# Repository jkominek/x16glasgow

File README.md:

# Commander X16 to Glasgow adapter

This is an expansion card for the [Commander
X16](https://x16community.github.io/faq/faq.html) retro PC, which
exposes one memory mapped IO region (at a time) to a [Glasgow
Interface Explorer](https://glasgow-embedded.org/latest/intro.html).

With it, the Glasgow can emulate nearly any IO card you might plug
into the X16, so long as that card only wants to talk to a modern
USB-capable PC 🤓. So far I've [got an
applet](https://github.com/jkominek/glasgow) which half-assedly
emulates a 16550, and hooks it up to a pseudoterminal on a Linux
system. With David Murray's ROMTERM, you can then use the X16 as
a "serial" terminal to log into the Linux system.

(To be super clear, that's all done without the [Commander X16 Serial
& ESP32 Network
card](https://texelec.com/product/commander-x16-serial-network-card/).)

And here's a quick little video of it in operation: https://www.youtube.com/watch?v=3OkkUSMPfc0

# how it works

The Glasgow has 16 IO pins. To act as an IO device, you need to handle:
- 8 data lines
- RWB
- PHI2
- At least one of the IO selection lines
- An IRQ
- Five address lines (for the full 32 byte space)

That's 17 lines. You could drop the IRQ line, but that'd be boring.
Instead, we decode RWB, PHI2 and a jumper-chosen IO selection line
using some 74-series logic, and condense the three of them into
/RD and /WR lines. That fits everything into 16 pins.

# how do i get a getty on a pseudoterminal

```
mgetty -r -b -m '""' /dev/pts/X
```

not actually sure if the `-b` is necessary. The `-m` bit was the secret
sauce.

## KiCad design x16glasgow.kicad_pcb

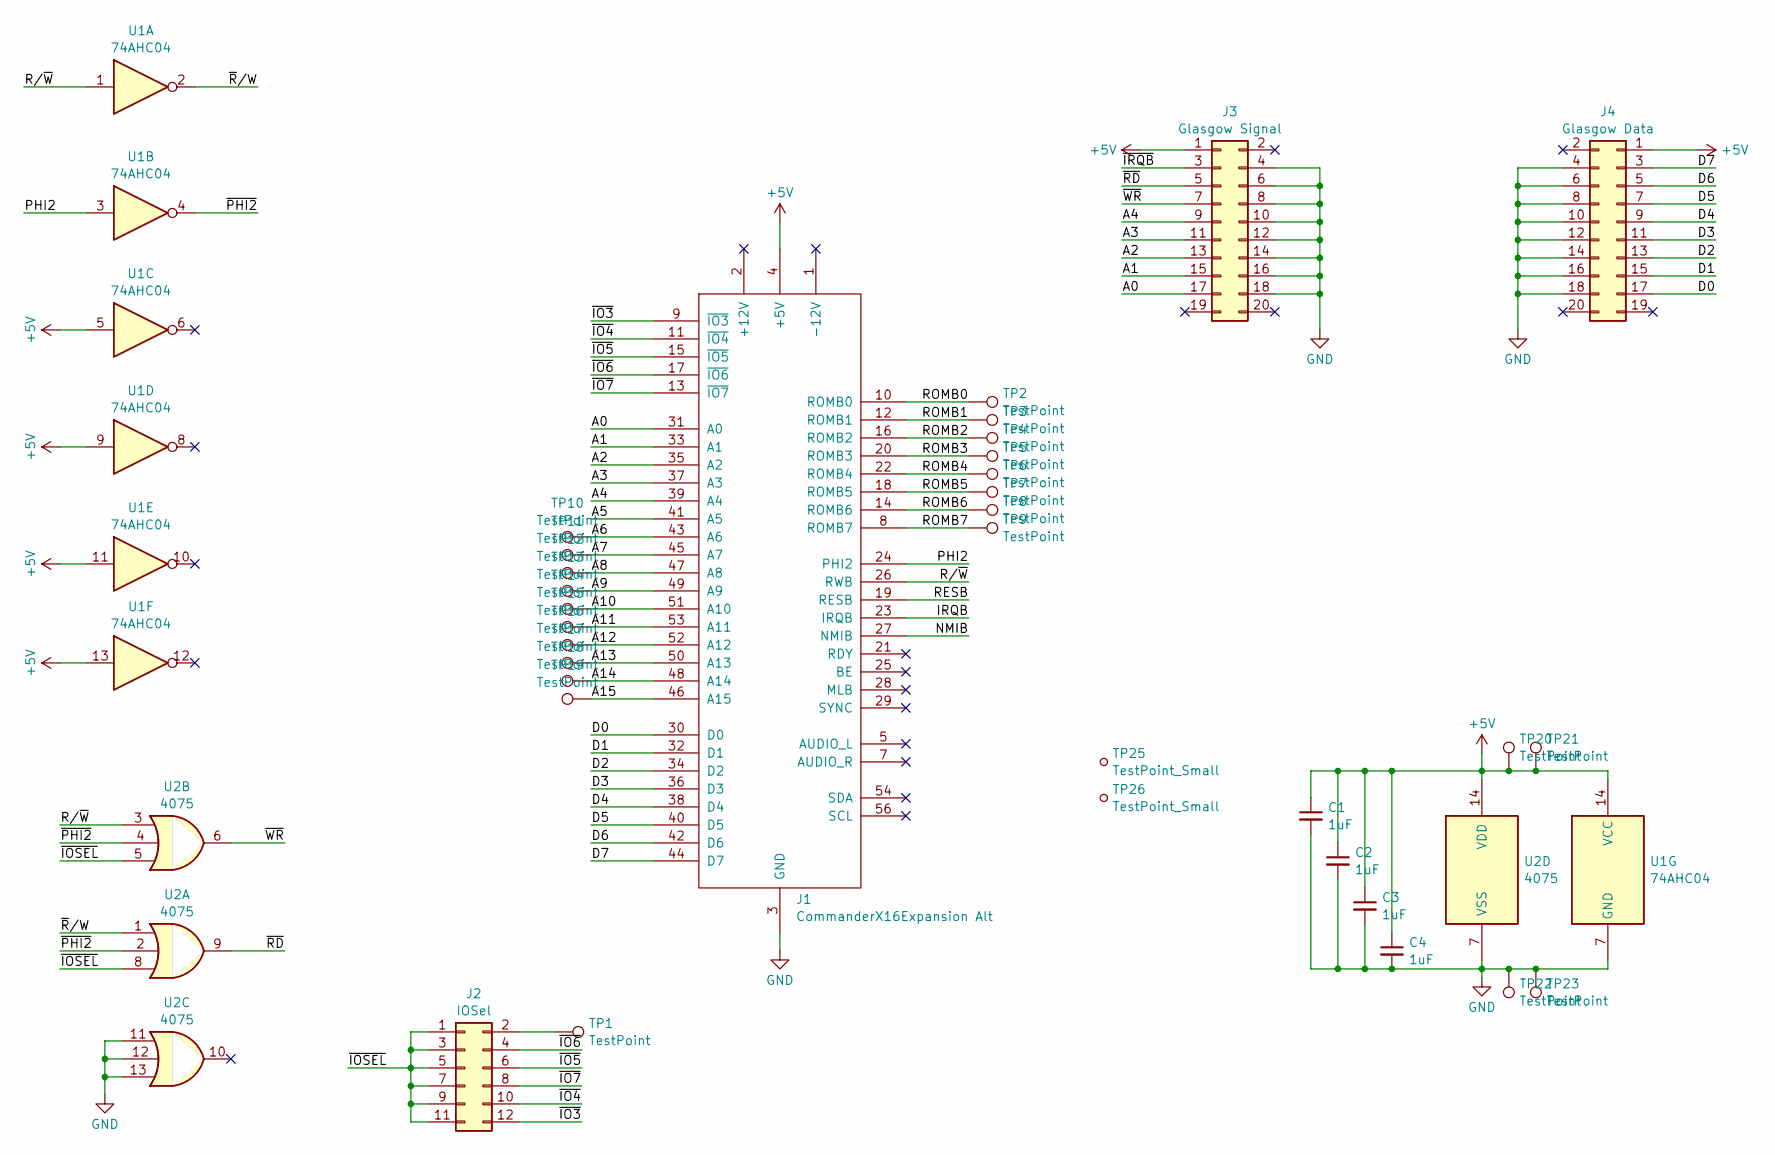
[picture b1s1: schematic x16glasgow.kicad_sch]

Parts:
C1, C2, C3, C4: 1uF; C_0805_2012Metric
J1: CommanderX16Expansion Alt; CommanderX16Expansion
J2: IOSel; PinHeader_2x06_P2.54mm_Vertical
J3: Glasgow Signal; PinSocket_2x10_P2.54mm_Vertical
J4: Glasgow Data; PinSocket_2x10_P2.54mm_Vertical
TP1, TP2, TP3, TP4, TP5, TP6, TP7, TP8, TP9, TP10, TP11, TP12, TP13, TP14, TP15, TP16, TP17, TP18, TP19, TP20, TP21, TP22, TP23: TestPoint; TestPoint_Pad_D2.0mm
TP25, TP26: TestPoint_Small; TSSOP-14_4.4x5mm_P0.65mm
U1: 74AHC04; TSSOP-14_4.4x5mm_P0.65mm
U2: 4075; TSSOP-14_4.4x5mm_P0.65mm

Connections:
+5V: C1.1, C2.1, C3.1, C4.1, J1.4 (+5V), J1.57 (+5V), J3.1, J4.1, TP20.1, TP21.1, U1.5, U1.9, U1.11, U1.13, U1.14 (VCC), U2.14 (VDD)
/A0: J1.31 (A0), J3.17
/A1: J1.33 (A1), J3.15
/A2: J1.35 (A2), J3.13
/A3: J1.37 (A3), J3.11
/A4: J1.39 (A4), J3.9
/A5: J1.41 (A5)
/A6: J1.43 (A6), TP10.1
/A7: J1.45 (A7), TP11.1
/A8: J1.47 (A8), TP12.1
/A9: J1.49 (A9), TP13.1
/A10: J1.51 (A10), TP14.1
/A11: J1.53 (A11), TP15.1
/A12: J1.52 (A12), TP16.1
/A13: J1.50 (A13), TP17.1
/A14: J1.48 (A14), TP18.1
/A15: J1.46 (A15), TP19.1
/D0: J1.30 (D0), J4.17
/D1: J1.32 (D1), J4.15
/D2: J1.34 (D2), J4.13
/D3: J1.36 (D3), J4.11
/D4: J1.38 (D4), J4.9
/D5: J1.40 (D5), J4.7
/D6: J1.42 (D6), J4.5
/D7: J1.44 (D7), J4.3
/IRQB: J1.23 (IRQB)
/NMIB: J1.27 (NMIB)
/PHI2: J1.24 (PHI2), U1.3
/RESB: J1.19 (RESB)
/ROMB0: J1.10 (ROMB0), TP2.1
/ROMB1: J1.12 (ROMB1), TP3.1
/ROMB2: J1.16 (ROMB2), TP4.1
/ROMB3: J1.20 (ROMB3), TP5.1
/ROMB4: J1.22 (ROMB4), TP6.1
/ROMB5: J1.18 (ROMB5), TP7.1
/ROMB6: J1.14 (ROMB6), TP8.1
/ROMB7: J1.8 (ROMB7), TP9.1
/R/~W: J1.26 (RWB), U1.1, U2.3
/~IO3: J1.9 (~IO3), J2.12
/~IO4: J1.11 (~IO4), J2.10
/~IO5: J1.15 (~IO5), J2.6
/~IO6: J1.17 (~IO6), J2.4
/~IO7: J1.13 (~IO7), J2.8
/~IOSEL: J2.1, J2.3, J2.5, J2.7, J2.9, J2.11, U2.5, U2.8
/~IRQB: J3.3
/~PHI2: U1.4, U2.2, U2.4
/~RD: J3.5, U2.9
/~R/W: U1.2, U2.1
/~WR: J3.7, U2.6
GND: C1.2, C2.2, C3.2, C4.2, J1.3 (GND), J1.6 (GND), J1.55 (GND), J1.58 (GND), J3.4, J3.6, J3.8, J3.10, J3.12, J3.14, J3.16, J3.18, J4.4, J4.6, J4.8, J4.10, J4.12, J4.14, J4.16, J4.18, TP22.1, TP23.1, U1.7 (GND), U2.7 (VSS), U2.11, U2.12, U2.13
unnamed: J2.2, TP1.1

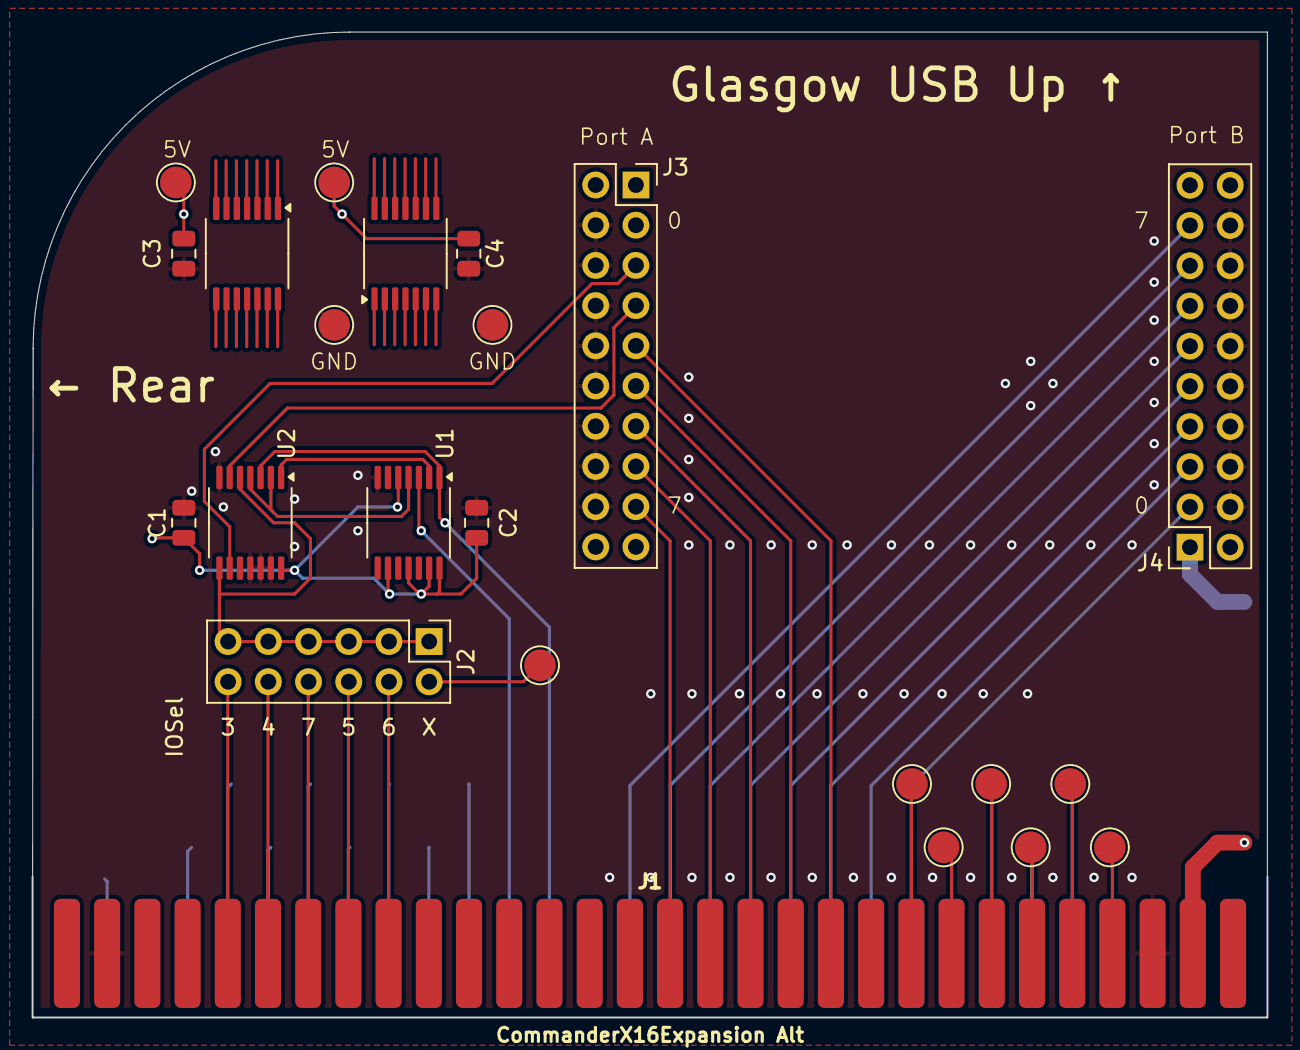
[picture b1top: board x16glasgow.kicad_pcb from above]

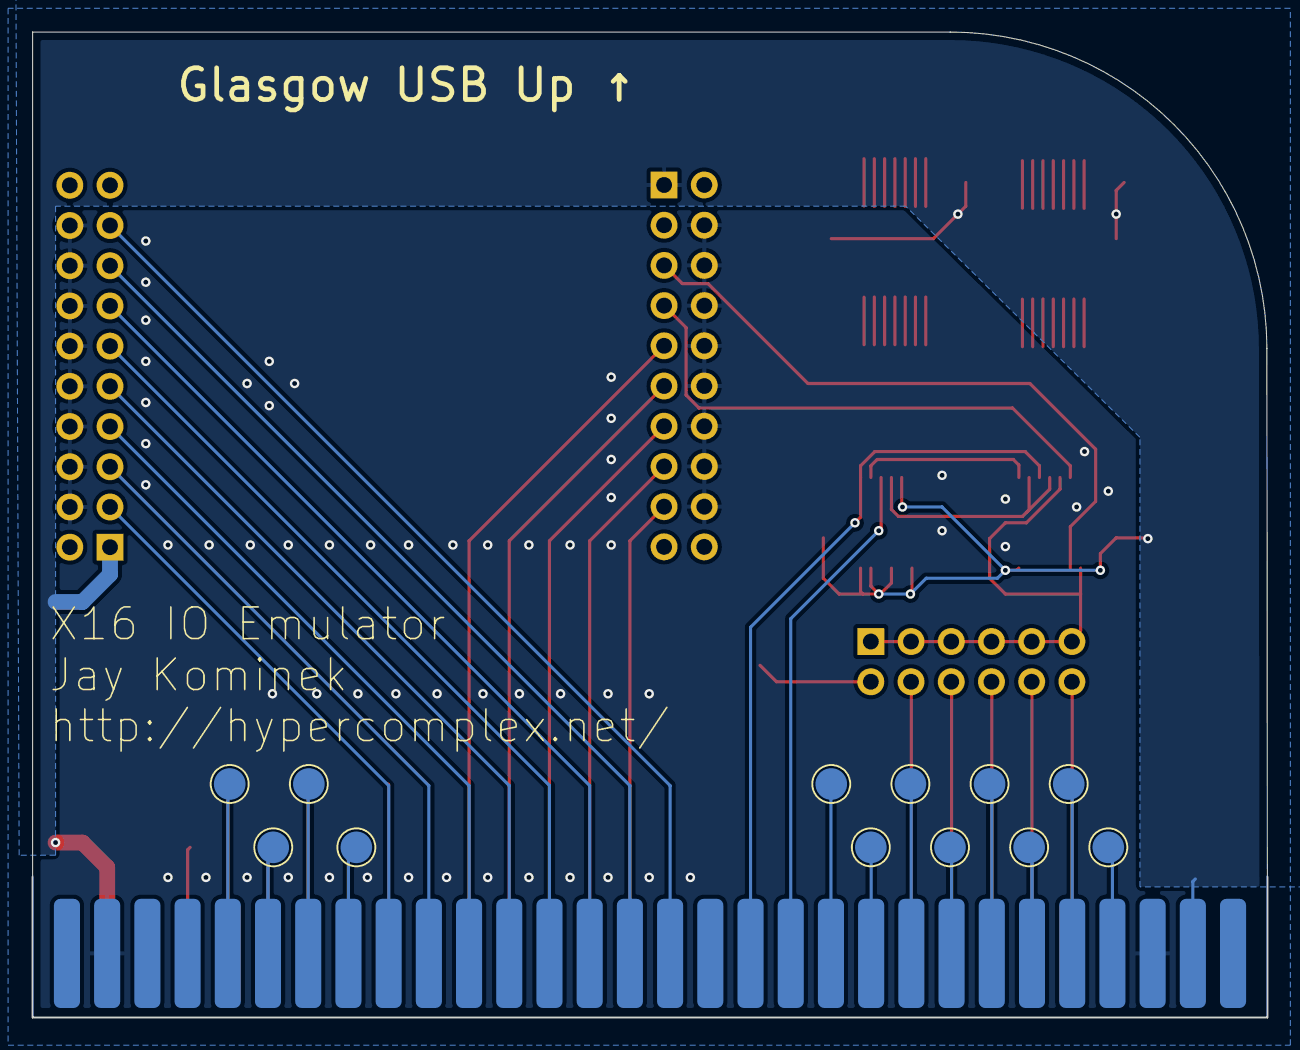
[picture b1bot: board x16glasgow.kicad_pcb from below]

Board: 2 copper layers, 78.0 x 62.2 mm, 35 parts (12 on the bottom side), 46 nets.

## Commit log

2024-06-07 add a render to the README
2024-06-07 pedantic clarification
